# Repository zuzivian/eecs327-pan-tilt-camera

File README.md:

# FaceAssure
A security camera product that presents that tracks a person's face using openCV in the cloud.

## Description
We are developing a security camera product called FaceAssure that presents the operator a comprehensive view of the area, and a person’s face as it moves across an area, using computer vision and multiple installed cameras. The owner is notified when an unknown person is detected so that they can investigate the situation.

We chose our project because we were interested making it useable for anti-theft purposes at home. Our first idea was to create a network of cameras linked together by a central server that provided an administrative overview for the homeowner. The pan and tilt servos made the most sense in helping a security system cover a large angle in the room. Finally, our interest in exploring computer vision made it possible to control servos autonomous using facial detection.

## More Information
For more description and build instructions, find out more at the Hackaday.io project link
https://hackaday.io/project/166037-faceassure-cloud-based-pan-tilt-security-camera

## Authors
- Nathaniel Wong (@zuzivian)
- Qiankai Cao (@QianKaiCao)

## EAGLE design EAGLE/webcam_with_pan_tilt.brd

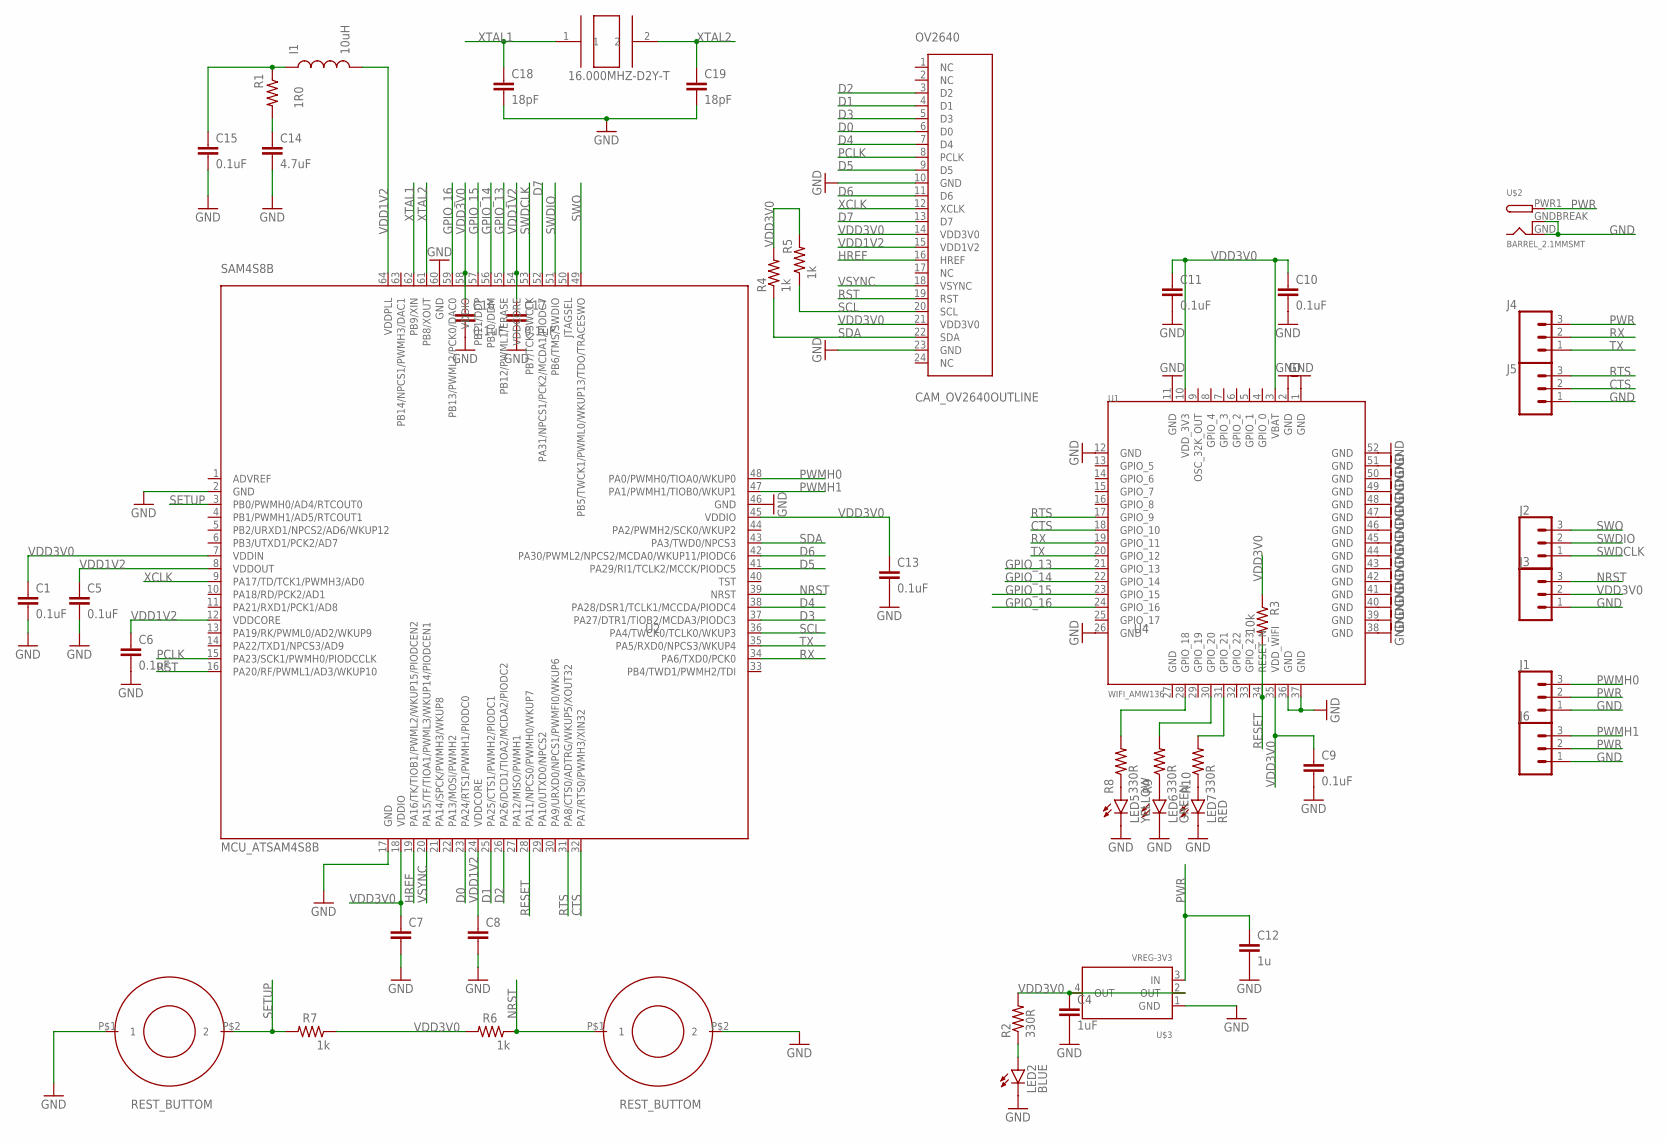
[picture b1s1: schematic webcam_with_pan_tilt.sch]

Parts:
16.000MHZ-D2Y-T: XTAL_12MHZ; ABM7-16.000MHZ-D2Y-T
C1, C5, C6, C9, C10, C11, C13, C15, C16, C17: 0.1uF; 0805
C4: 1uF; 0805
C7, C8: CAP; 0805
C12: 1u; 0805
C14: 4.7uF; 0805
C18, C19: 18pF; 0805
I1: 10uH; 0805
J1, J2, J3, J4, J5, J6: CONN_03; 1X03
LED2: BLUE; LED-0603
LED5: YELLOW; LED-0603
LED6: GREEN; LED-0603
LED7: RED; LED-0603
OV2640: CAM_OV2640OUTLINE; CAM_CONN
R1: 1R0; 0805
R2, R8, R9, R10: 330R; 0805
R3: 10k; 0805
R4, R5, R6, R7: 1k; 0805
SAM4S8B: MCU_ATSAM4S8B; QFP50P1200X1200X160-64N
U1: WIFI_AMW136; AMW136
U2, U4: REST_BUTTOM; BTN_2
U$2: BARREL_2.1MMSMT; DCJACK_2MM_SMT
U$3: VREG-3V3; R-PDSO-G4_TI

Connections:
CTS: J5.2, SAM4S8B.32 (PA7/RTS0/PWMH3/XIN32), U1.18 (GPIO_10)
D0: OV2640.6 (D0), SAM4S8B.23 (PA24/RTS1/PWMH1/PIODC0)
D1: OV2640.4 (D1), SAM4S8B.25 (PA25/CTS1/PWMH2/PIODC1)
D2: OV2640.3 (D2), SAM4S8B.26 (PA26/DCD1/TIOA2/MCDA2/PIODC2)
D3: OV2640.5 (D3), SAM4S8B.37 (PA27/DTR1/TIOB2/MCDA3/PIODC3)
D4: OV2640.7 (D4), SAM4S8B.38 (PA28/DSR1/TCLK1/MCCDA/PIODC4)
D5: OV2640.9 (D5), SAM4S8B.41 (PA29/RI1/TCLK2/MCCK/PIODC5)
D6: OV2640.11 (D6), SAM4S8B.42 (PA30/PWML2/NPCS2/MCDA0/WKUP11/PIODC6)
D7: OV2640.13 (D7), SAM4S8B.52 (PA31/NPCS1/PCK2/MCDA1/PIODC7)
GND: C1.2, C4.2, C5.2, C6.2, C7.2, C8.2, C9.2, C10.2, C11.2, C12.2, C13.2, C14.2, C15.2, C16.2, C17.2, C18.2, C19.2, J1.1, J3.1, J5.1, J6.1, LED2.C, LED5.C, LED6.C, LED7.C, OV2640.10 (GND), OV2640.23 (GND), SAM4S8B.2 (GND), SAM4S8B.17 (GND), SAM4S8B.46 (GND), SAM4S8B.60 (GND), U1.1 (GND), U1.2 (GND), U1.11 (GND), U1.12 (GND), U1.26 (GND), U1.36 (GND), U1.37 (GND), U1.38 (GND), U1.39 (GND), U1.40 (GND), U1.41 (GND), U1.42 (GND), U1.43 (GND), U1.44 (GND), U1.45 (GND), U1.46 (GND), U1.47 (GND), U1.48 (GND), U1.49 (GND), U1.50 (GND), U1.51 (GND), U1.52 (GND), U2.P$1 (1), U4.P$2 (2), U$2.GND, U$2.GNDBREAK, U$3.1 (GND)
GPIO_13: SAM4S8B.55 (PB12/PWML1/ERASE), U1.21 (GPIO_13)
GPIO_14: SAM4S8B.56 (PB10/DDM), U1.22 (GPIO_14)
GPIO_15: SAM4S8B.57 (PB11/DDP), U1.23 (GPIO_15)
GPIO_16: SAM4S8B.59 (PB13/PWML2/PCK0/DAC0), U1.24 (GPIO_16)
HREF: OV2640.16 (HREF), SAM4S8B.19 (PA16/TK/TIOB1/PWML2/WKUP15/PIODCEN2)
unnamed: C14.1, R1.2
unnamed: C15.1, I1.1, R1.1
unnamed: LED5.A, R8.1
unnamed: LED6.A, R9.1
unnamed: R8.2, U1.28 (GPIO_18)
unnamed: LED2.A, R2.1
unnamed: LED7.A, R10.1
unnamed: R9.2, U1.30 (GPIO_20)
unnamed: R10.2, U1.31 (GPIO_21)
NRST: J3.3, R6.1, SAM4S8B.39 (NRST), U4.P$1 (1)
PCLK: OV2640.8 (PCLK), SAM4S8B.15 (PA23/SCK1/PWMH0/PIODCCLK)
PWMH0: J1.3, SAM4S8B.48 (PA0/PWMH0/TIOA0/WKUP0)
PWMH1: J6.3, SAM4S8B.47 (PA1/PWMH1/TIOB0/WKUP1)
PWR: C12.1, J1.2, J4.3, J6.2, U$2.PWR1 (PWR), U$3.3 (IN)
RESET: R3.2, SAM4S8B.28 (PA11/NPCS0/PWMH0/WKUP7), U1.34 (RESET_N)
RST: OV2640.19 (RST), SAM4S8B.16 (PA20/RF/PWML1/AD3/WKUP10)
RTS: J5.3, SAM4S8B.31 (PA8/CTS0/ADTRG/WKUP5/XOUT32), U1.17 (GPIO_9)
RX: J4.2, SAM4S8B.34 (PA6/TXD0/PCK0), U1.19 (GPIO_11)
SCL: OV2640.20 (SCL), R5.1, SAM4S8B.36 (PA4/TWCK0/TCLK0/WKUP3)
SDA: OV2640.22 (SDA), R4.1, SAM4S8B.43 (PA3/TWD0/NPCS3)
SETUP: R7.2, SAM4S8B.3 (PB0/PWMH0/AD4/RTCOUT0), U2.P$2 (2)
SWDCLK: J2.1, SAM4S8B.53 (PB7/TCK/SWCLK)
SWDIO: J2.2, SAM4S8B.51 (PB6/TMS/SWDIO)
SWO: J2.3, SAM4S8B.49 (PB5/TWCK1/PWML0/WKUP13/TDO/TRACESWO)
TX: J4.1, SAM4S8B.35 (PA5/RXD0/NPCS3/WKUP4), U1.20 (GPIO_12)
VDD1V2: C5.1, C6.1, C8.1, C17.1, I1.2, OV2640.15 (VDD1V2), SAM4S8B.8 (VDDOUT), SAM4S8B.12 (VDDCORE), SAM4S8B.24 (VDDCORE), SAM4S8B.54 (VDDCORE), SAM4S8B.64 (VDDPLL)
VDD3V0: C1.1, C4.1, C7.1, C9.1, C10.1, C11.1, C13.1, C16.1, J3.2, OV2640.14 (VDD3V0), OV2640.21 (VDD3V0), R2.2, R3.1, R4.2, R5.2, R6.2, R7.1, SAM4S8B.7 (VDDIN), SAM4S8B.18 (VDDIO), SAM4S8B.45 (VDDIO), SAM4S8B.58 (VDDIO), U1.3 (VBAT), U1.10 (VDD_3V3), U1.35 (VDD_WIFI), U$3.2 (OUT), U$3.4 (OUT)
VSYNC: OV2640.18 (VSYNC), SAM4S8B.20 (PA15/TF/TIOA1/PWML3/WKUP14/PIODCEN1)
XCLK: OV2640.12 (XCLK), SAM4S8B.9 (PA17/TD/TCK1/PWMH3/AD0)
XTAL1: 16.000MHZ-D2Y-T.1, C18.1, SAM4S8B.62 (PB9/XIN)
XTAL2: 16.000MHZ-D2Y-T.2, C19.1, SAM4S8B.61 (PB8/XOUT)

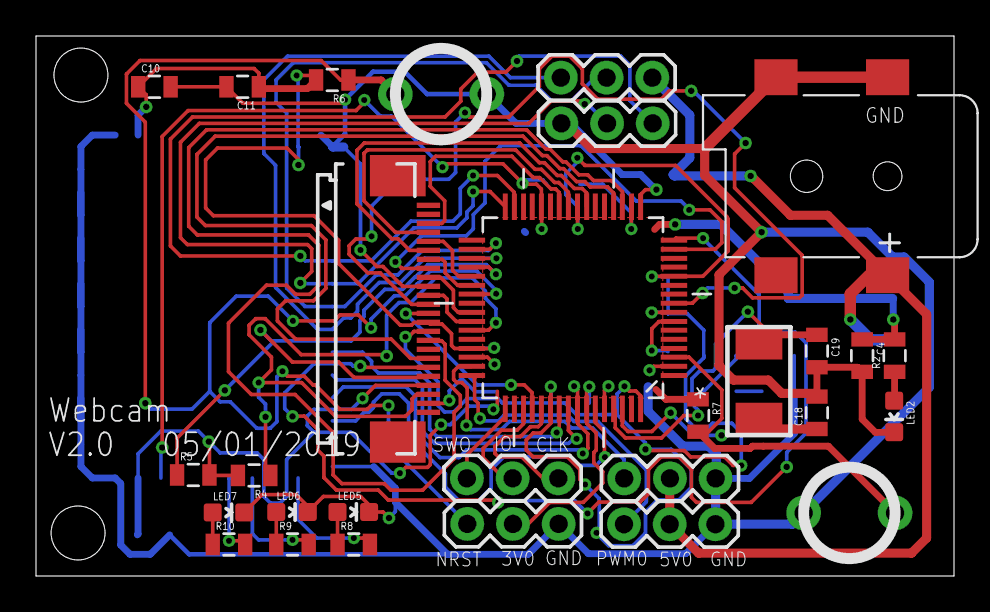
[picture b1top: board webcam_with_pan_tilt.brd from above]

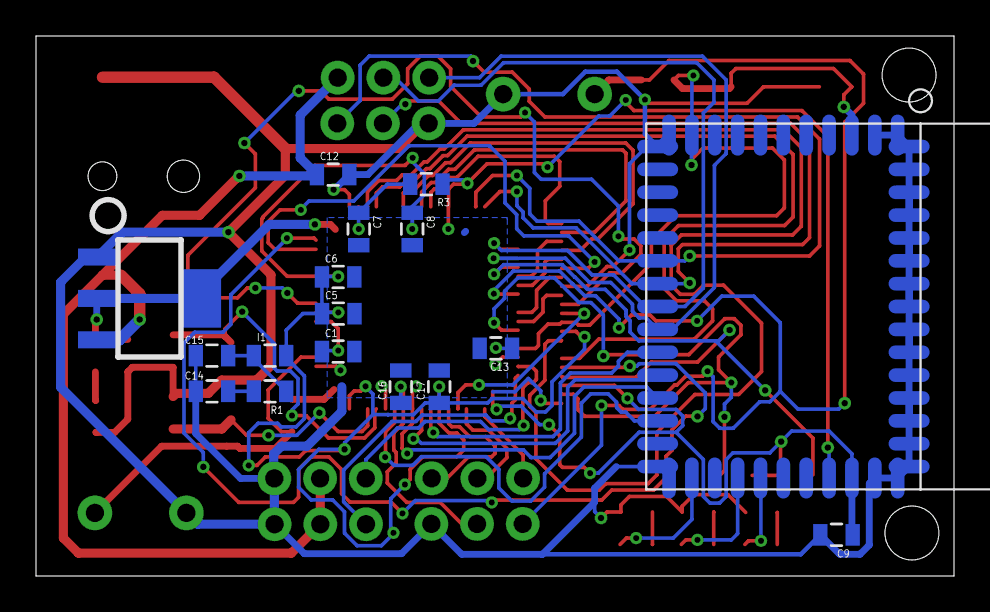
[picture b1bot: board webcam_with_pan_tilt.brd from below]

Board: 2 copper layers, 51.0 x 30.0 mm, 46 parts (17 on the bottom side), 46 nets.

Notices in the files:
parts and their libraries:
SparkFun-Connectors: Licensing: Creative Commons ShareAlike 4.0 International - https://creativecommons.org/licenses/by-sa/4.0
